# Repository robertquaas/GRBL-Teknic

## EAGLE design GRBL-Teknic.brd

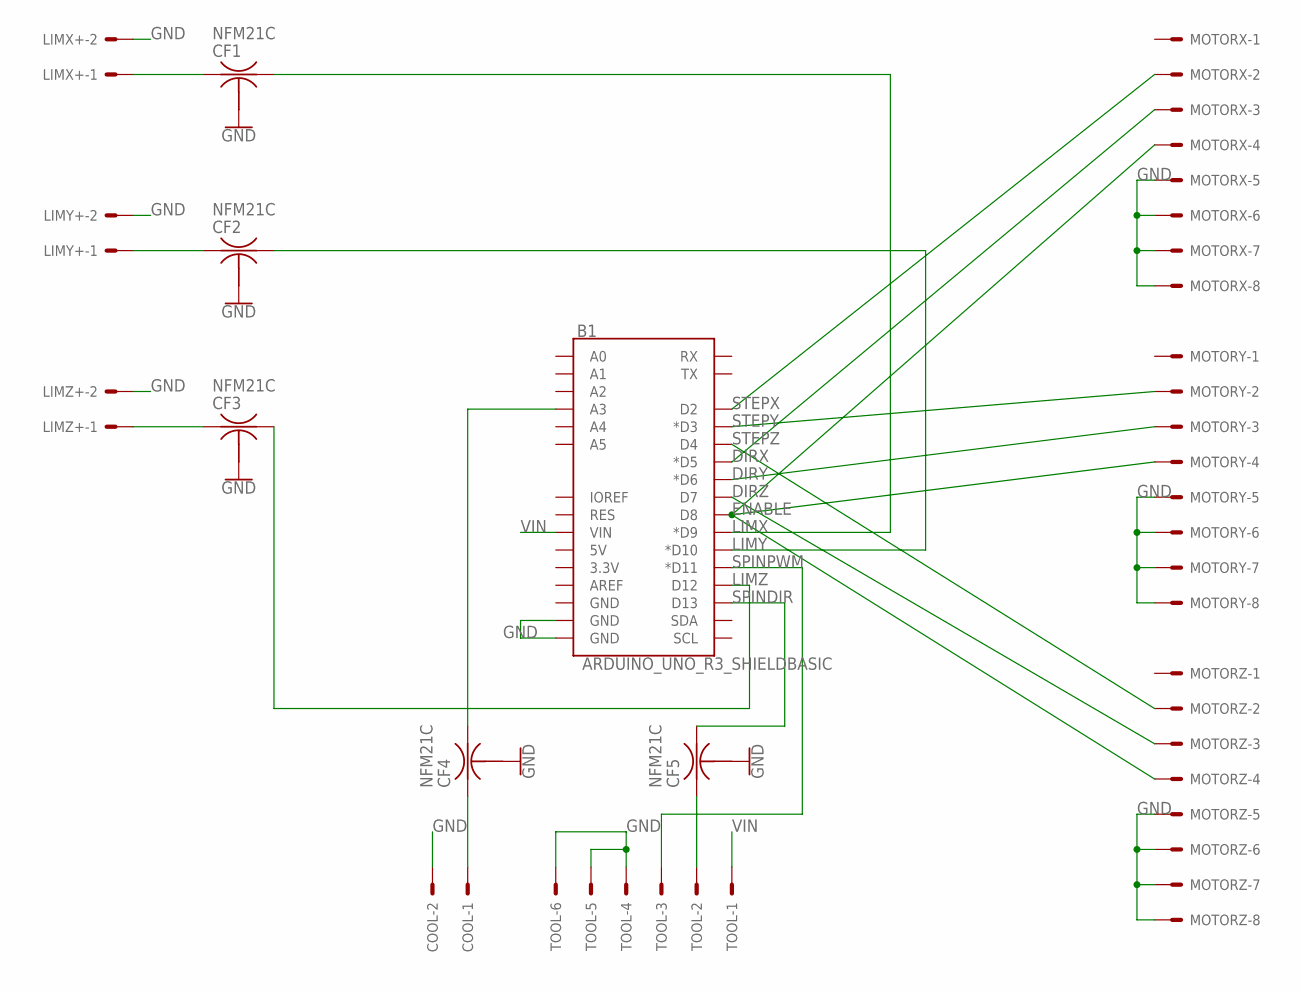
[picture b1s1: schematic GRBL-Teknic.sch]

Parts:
B1: ARDUINO_UNO_R3_SHIELDBASIC; UNO_R3_SHIELD
CF1, CF2, CF3, CF4, CF5: NFM21C
COOL: 555X-2V; 5566-2
LIMX+: 555X-2V; 5566-2
LIMY+: 555X-2V; 5566-2
LIMZ+: 555X-2V; 5566-2
MOTORX: 555X-8V; 5566-8
MOTORY: 555X-8V; 5566-8
MOTORZ: 555X-8V; 5566-8
TOOL: 555X-6V; 5566-6

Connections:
COOL: B1.A3, CF4.3
DIRX: B1.D5 (*D5), MOTORX.3
DIRY: B1.D6 (*D6), MOTORY.3
DIRZ: B1.D7, MOTORZ.3
ENABLE: B1.D8, MOTORX.4, MOTORY.4, MOTORZ.4
GND: B1.GND@0 (GND), B1.GND@1 (GND), CF1.2@1 (2), CF2.2@1 (2), CF3.2@1 (2), CF4.2@1 (2), CF5.2@1 (2), COOL.2, LIMX+.2, LIMY+.2, LIMZ+.2, MOTORX.5, MOTORX.6, MOTORX.7, MOTORX.8, MOTORY.5, MOTORY.6, MOTORY.7, MOTORY.8, MOTORZ.5, MOTORZ.6, MOTORZ.7, MOTORZ.8, TOOL.4, TOOL.5, TOOL.6
LIMX: B1.D9 (*D9), CF1.3
LIMY: B1.D10 (*D10), CF2.3
LIMZ: B1.D12, CF3.3
unnamed: CF4.1, COOL.1
unnamed: CF5.1, TOOL.2
unnamed: CF1.1, LIMX+.1
unnamed: CF2.1, LIMY+.1
unnamed: CF3.1, LIMZ+.1
SPINDIR: B1.D13, CF5.3
SPINPWM: B1.D11 (*D11), TOOL.3
STEPX: B1.D2, MOTORX.2
STEPY: B1.D3 (*D3), MOTORY.2
STEPZ: B1.D4, MOTORZ.2
VIN: B1.VIN, TOOL.1

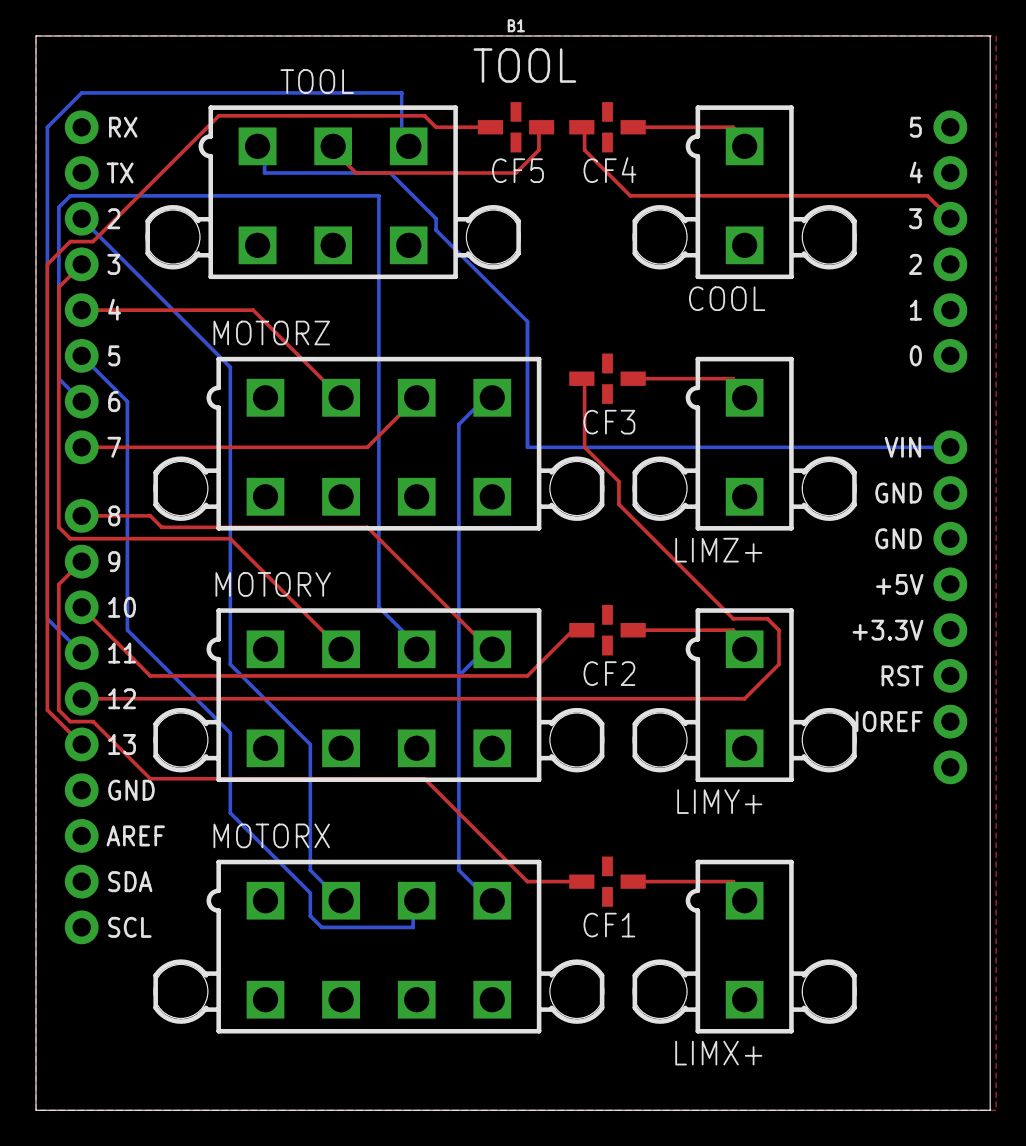
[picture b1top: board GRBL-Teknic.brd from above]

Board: 2 copper layers, 53.0 x 59.7 mm, 14 parts (0 on the bottom side), 20 nets.

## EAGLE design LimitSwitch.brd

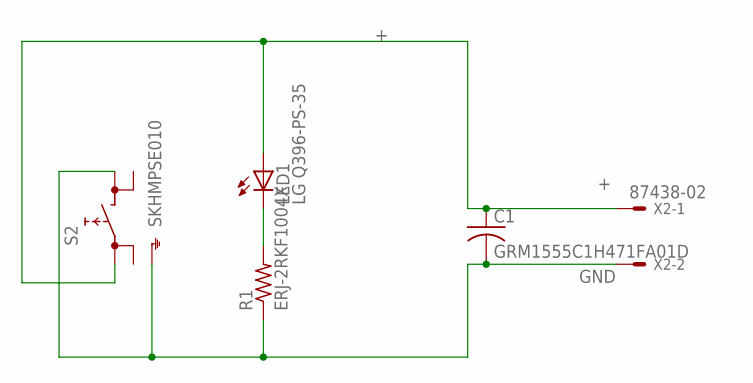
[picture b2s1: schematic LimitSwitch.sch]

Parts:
C1: GRM1555C1H471FA01D; C0402
LED1: LG Q396-PS-35; CHIPLED_0603
R1: ERJ-2RKF1004X; R0402
S2: SKHMPSE010; SKHMPXE010
X2: 87438-02

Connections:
+: C1.1, LED1.A, S2.1 (1.1), X2.1
GND: C1.2, R1.1, S2.3 (2.1), S2.5 (SH), X2.2
unnamed: LED1.C, R1.2

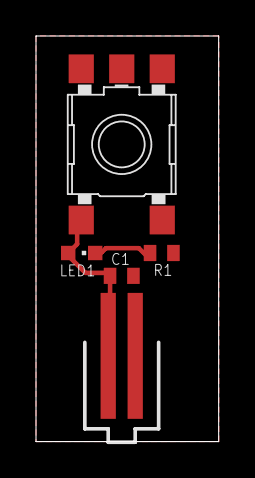
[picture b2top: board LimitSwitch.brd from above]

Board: 2 copper layers, 10.1 x 22.5 mm, 5 parts (0 on the bottom side), 3 nets.

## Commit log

2017-02-05 initial add starting from sparkfun arduino
2017-02-05 going with redboard -- need the USB port
2017-02-06 working from adafruit metro now, simpest i could find
2017-02-09 added in motor and limit connectors
2017-02-10 fixes #1 fixes #2
2017-02-10 fixes #4
2017-02-20 ready to try sample order
2017-02-20 updated with coolant connection
2017-02-20 designed multi direction limit switch
2017-02-20 much smaller switch
2017-02-21 sent off an order
2017-02-27 updated as I learn more from EMI filtering

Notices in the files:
parts and their libraries:
SparkFun-Boards: Licensing: Creative Commons ShareAlike 4.0 International - https://creativecommons.org/licenses/by-sa/4.0
